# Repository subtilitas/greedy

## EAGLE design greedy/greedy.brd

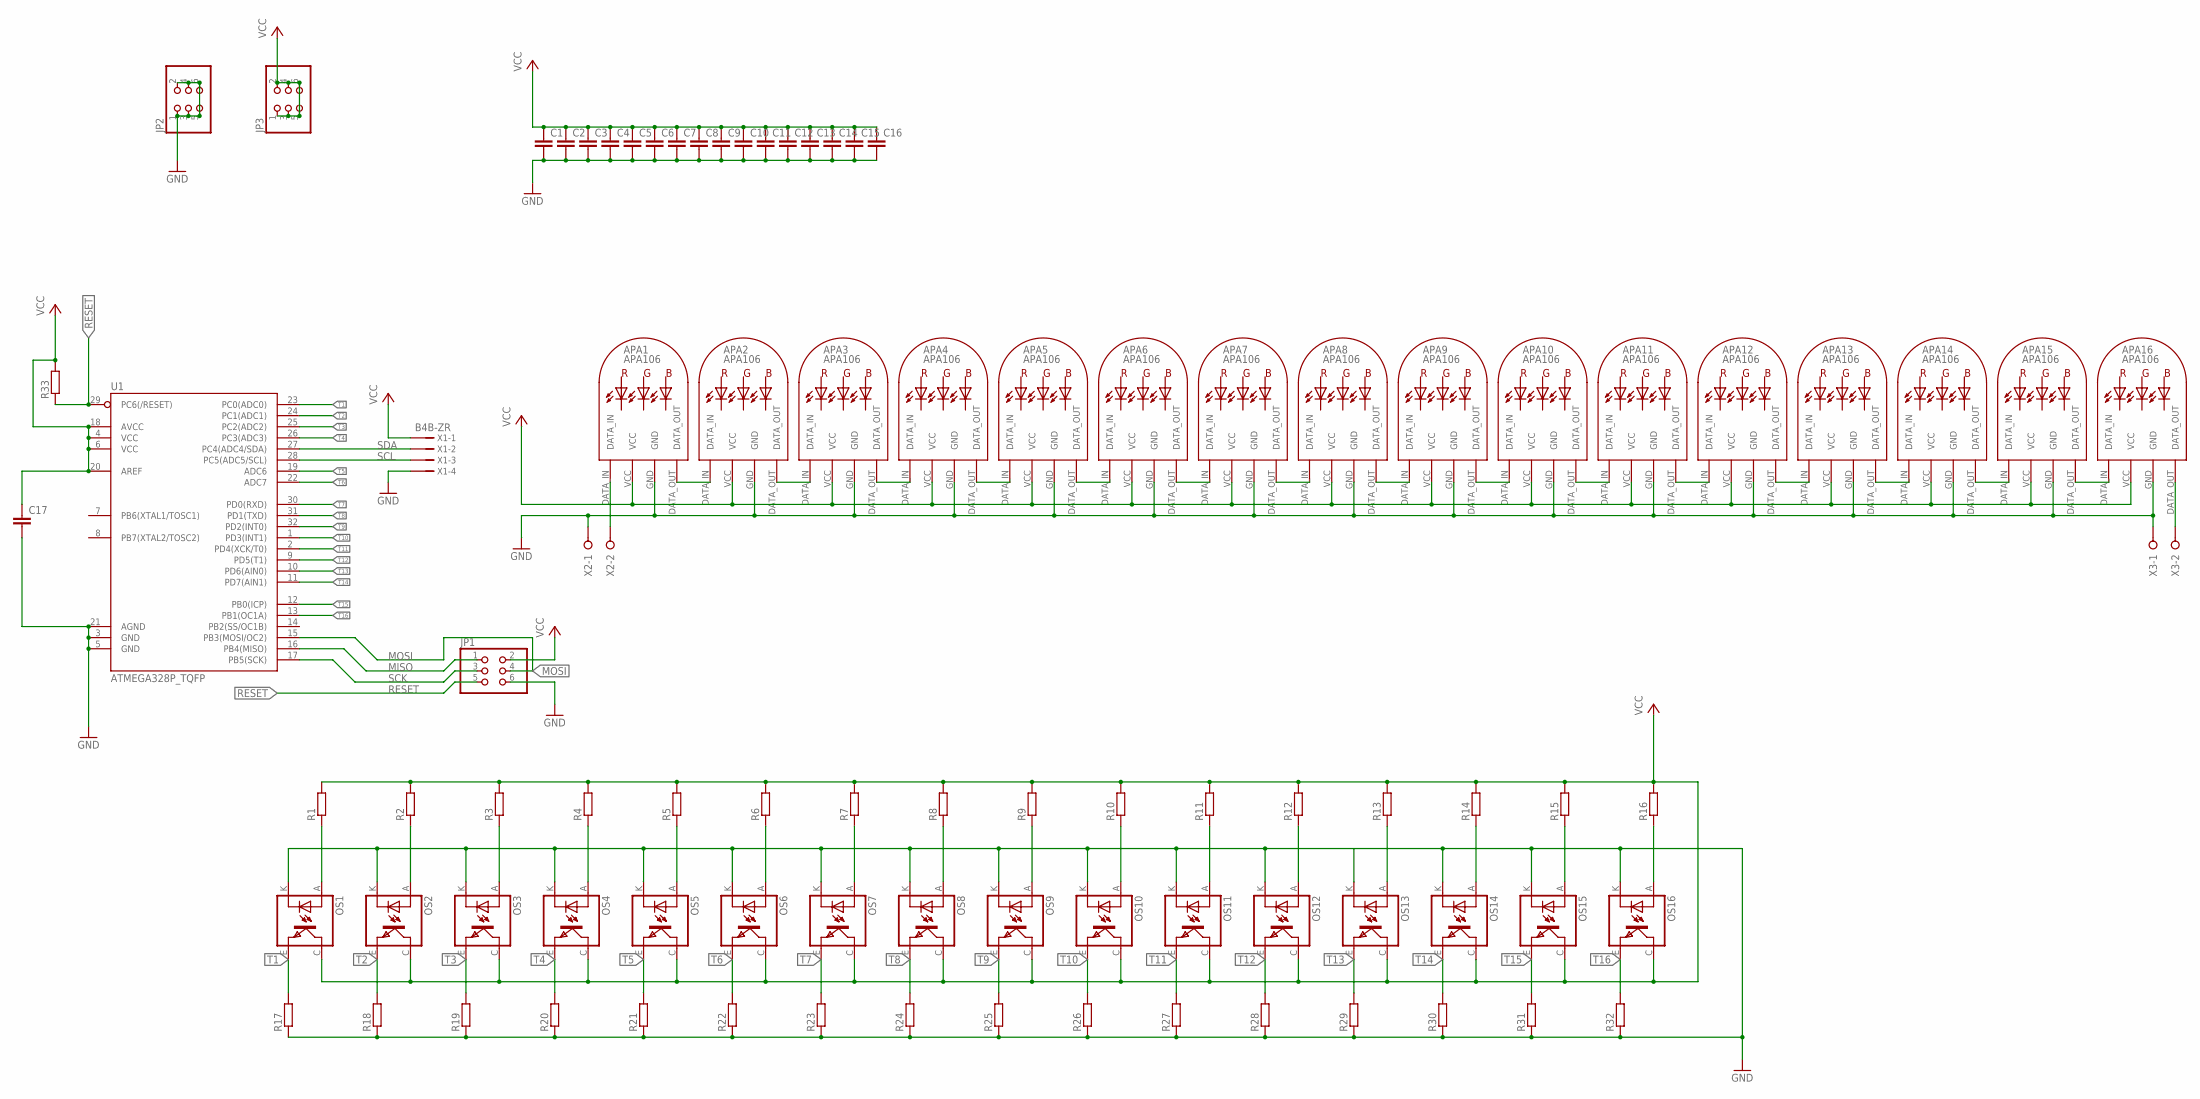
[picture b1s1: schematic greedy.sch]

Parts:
APA1, APA2, APA3, APA4, APA5, APA6, APA7, APA8, APA9, APA10, APA11, APA12, APA13, APA14, APA15, APA16: APA106; APA_106_8MM
C1, C2, C3, C4, C5, C6, C7, C8, C9, C10, C11, C12, C13, C14, C15, C16: C5/3; C5B3
C17: C-EU025-025X050; C025-025X050
JP1, JP2, JP3: PINHD-2X3; 2X03
OS1, OS2, OS3, OS4, OS5, OS6, OS7, OS8, OS9, OS10, OS11, OS12, OS13, OS14, OS15, OS16: TCRT5000
R1, R2, R3, R4, R5, R6, R7, R8, R9, R10, R11, R12, R13, R14, R15, R16, R17, R18, R19, R20, R21, R22, R23, R24, R25, R26, R27, R28, R29, R30, R31, R32, R33: R-EU_R0805; R0805
U1: ATMEGA328P_TQFP; TQFP32-08
X1: B4B-ZR
X2, X3: W237-02P; W237-132

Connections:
GND: APA1.GND, APA2.GND, APA3.GND, APA4.GND, APA5.GND, APA6.GND, APA7.GND, APA8.GND, APA9.GND, APA10.GND, APA11.GND, APA12.GND, APA13.GND, APA14.GND, APA15.GND, APA16.GND, C1.2, C2.2, C3.2, C4.2, C5.2, C6.2, C7.2, C8.2, C9.2, C10.2, C11.2, C12.2, C13.2, C14.2, C15.2, C16.2, C17.2, JP1.6, JP2.1, JP2.2, JP2.3, JP2.4, JP2.5, JP2.6, OS1.K (CATHODE), OS2.K (CATHODE), OS3.K (CATHODE), OS4.K (CATHODE), OS5.K (CATHODE), OS6.K (CATHODE), OS7.K (CATHODE), OS8.K (CATHODE), OS9.K (CATHODE), OS10.K (CATHODE), OS11.K (CATHODE), OS12.K (CATHODE), OS13.K (CATHODE), OS14.K (CATHODE), OS15.K (CATHODE), OS16.K (CATHODE), R17.1, R17.11 (1), R18.1, R18.11 (1), R19.1, R19.11 (1), R20.1, R20.11 (1), R21.1, R21.11 (1), R22.1, R22.11 (1), R23.1, R23.11 (1), R24.1, R24.11 (1), R25.1, R25.11 (1), R26.1, R26.11 (1), R27.1, R27.11 (1), R28.1, R28.11 (1), R29.1, R29.11 (1), R30.1, R30.11 (1), R31.1, R31.11 (1), R32.1, R32.11 (1), U1.3 (GND), U1.5 (GND), U1.21 (AGND), X1.4, X2.1, X3.1
MISO: JP1.1, U1.16 (PB4(MISO))
MOSI: JP1.4, U1.15 (PB3(MOSI/OC2))
unnamed: APA1.DATA_IN, X2.2
unnamed: OS1.A (ANODE), R1.1, R1.11 (1)
unnamed: OS2.A (ANODE), R2.1, R2.11 (1)
unnamed: OS3.A (ANODE), R3.1, R3.11 (1)
unnamed: OS4.A (ANODE), R4.1, R4.11 (1)
unnamed: OS5.A (ANODE), R5.1, R5.11 (1)
unnamed: OS6.A (ANODE), R6.1, R6.11 (1)
unnamed: OS7.A (ANODE), R7.1, R7.11 (1)
unnamed: OS8.A (ANODE), R8.1, R8.11 (1)
unnamed: OS9.A (ANODE), R9.1, R9.11 (1)
unnamed: OS10.A (ANODE), R10.1, R10.11 (1)
unnamed: OS11.A (ANODE), R11.1, R11.11 (1)
unnamed: OS12.A (ANODE), R12.1, R12.11 (1)
unnamed: OS13.A (ANODE), R13.1, R13.11 (1)
unnamed: OS14.A (ANODE), R14.1, R14.11 (1)
unnamed: OS15.A (ANODE), R15.1, R15.11 (1)
unnamed: OS16.A (ANODE), R16.1, R16.11 (1)
unnamed: APA16.DATA_OUT, X3.2
unnamed: APA1.DATA_OUT, APA2.DATA_IN
unnamed: APA2.DATA_OUT, APA3.DATA_IN
unnamed: APA3.DATA_OUT, APA4.DATA_IN
unnamed: APA4.DATA_OUT, APA5.DATA_IN
unnamed: APA5.DATA_OUT, APA6.DATA_IN
unnamed: APA6.DATA_OUT, APA7.DATA_IN
unnamed: APA7.DATA_OUT, APA8.DATA_IN
unnamed: APA8.DATA_OUT, APA9.DATA_IN
unnamed: APA9.DATA_OUT, APA10.DATA_IN
unnamed: APA10.DATA_OUT, APA11.DATA_IN
unnamed: APA11.DATA_OUT, APA12.DATA_IN
unnamed: APA12.DATA_OUT, APA13.DATA_IN
unnamed: APA13.DATA_OUT, APA14.DATA_IN
unnamed: APA14.DATA_OUT, APA15.DATA_IN
unnamed: APA15.DATA_OUT, APA16.DATA_IN
RESET: JP1.5, R33.1, R33.11 (1), U1.29 (PC6(/RESET))
SCK: JP1.3, U1.17 (PB5(SCK))
SCL: U1.28 (PC5(ADC5/SCL)), X1.3
SDA: U1.27 (PC4(ADC4/SDA)), X1.2
T1: OS1.E (EMITTER), R17.2, R17.21 (2), U1.23 (PC0(ADC0))
T2: OS2.E (EMITTER), R18.2, R18.21 (2), U1.24 (PC1(ADC1))
T3: OS3.E (EMITTER), R19.2, R19.21 (2), U1.25 (PC2(ADC2))
T4: OS4.E (EMITTER), R20.2, R20.21 (2), U1.26 (PC3(ADC3))
T5: OS5.E (EMITTER), R21.2, R21.21 (2), U1.19 (ADC6)
T6: OS6.E (EMITTER), R22.2, R22.21 (2), U1.22 (ADC7)
T7: OS7.E (EMITTER), R23.2, R23.21 (2), U1.30 (PD0(RXD))
T8: OS8.E (EMITTER), R24.2, R24.21 (2), U1.31 (PD1(TXD))
T9: OS9.E (EMITTER), R25.2, R25.21 (2), U1.32 (PD2(INT0))
T10: OS10.E (EMITTER), R26.2, R26.21 (2), U1.1 (PD3(INT1))
T11: OS11.E (EMITTER), R27.2, R27.21 (2), U1.2 (PD4(XCK/T0))
T12: OS12.E (EMITTER), R28.2, R28.21 (2), U1.9 (PD5(T1))
T13: OS13.E (EMITTER), R29.2, R29.21 (2), U1.10 (PD6(AIN0))
T14: OS14.E (EMITTER), R30.2, R30.21 (2), U1.11 (PD7(AIN1))
T15: OS15.E (EMITTER), R31.2, R31.21 (2), U1.12 (PB0(ICP))
T16: OS16.E (EMITTER), R32.2, R32.21 (2), U1.13 (PB1(OC1A))
VCC: APA1.VCC, APA2.VCC, APA3.VCC, APA4.VCC, APA5.VCC, APA6.VCC, APA7.VCC, APA8.VCC, APA9.VCC, APA10.VCC, APA11.VCC, APA12.VCC, APA13.VCC, APA14.VCC, APA15.VCC, APA16.VCC, C1.1, C2.1, C3.1, C4.1, C5.1, C6.1, C7.1, C8.1, C9.1, C10.1, C11.1, C12.1, C13.1, C14.1, C15.1, C16.1, C17.1, JP1.2, JP3.1, JP3.2, JP3.3, JP3.4, JP3.5, JP3.6, OS1.C (COLLECTOR), OS2.C (COLLECTOR), OS3.C (COLLECTOR), OS4.C (COLLECTOR), OS5.C (COLLECTOR), OS6.C (COLLECTOR), OS7.C (COLLECTOR), OS8.C (COLLECTOR), OS9.C (COLLECTOR), OS10.C (COLLECTOR), OS11.C (COLLECTOR), OS12.C (COLLECTOR), OS13.C (COLLECTOR), OS14.C (COLLECTOR), OS15.C (COLLECTOR), OS16.C (COLLECTOR), R1.2, R1.21 (2), R2.2, R2.21 (2), R3.2, R3.21 (2), R4.2, R4.21 (2), R5.2, R5.21 (2), R6.2, R6.21 (2), R7.2, R7.21 (2), R8.2, R8.21 (2), R9.2, R9.21 (2), R10.2, R10.21 (2), R11.2, R11.21 (2), R12.2, R12.21 (2), R13.2, R13.21 (2), R14.2, R14.21 (2), R15.2, R15.21 (2), R16.2, R16.21 (2), R33.2, R33.21 (2), U1.4 (VCC), U1.6 (VCC), U1.18 (AVCC), U1.20 (AREF), X1.1

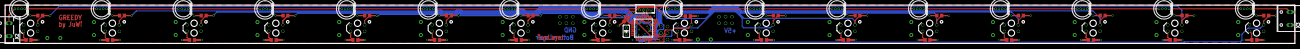
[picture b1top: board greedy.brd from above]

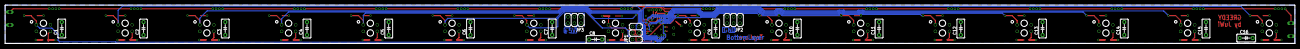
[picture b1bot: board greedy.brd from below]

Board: 4 copper layers, 505.0 x 15.0 mm, 89 parts (19 on the bottom side), 57 nets.

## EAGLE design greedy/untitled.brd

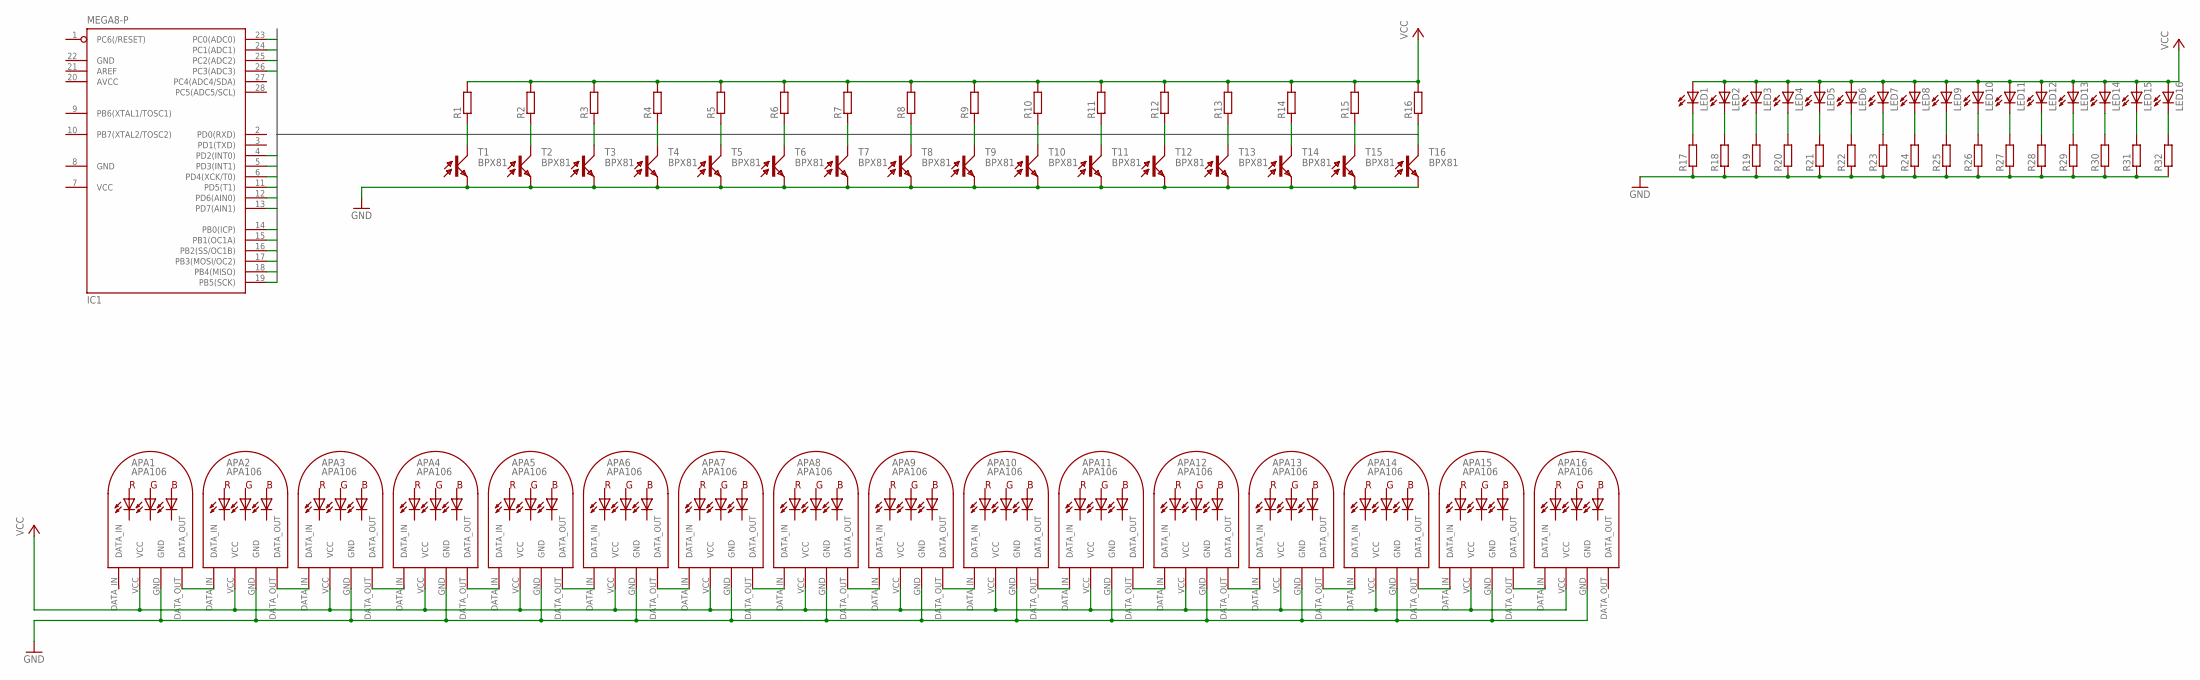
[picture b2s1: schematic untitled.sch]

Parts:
APA1, APA2, APA3, APA4, APA5, APA6, APA7, APA8, APA9, APA10, APA11, APA12, APA13, APA14, APA15, APA16: APA106; APA_106_8MM
IC1: MEGA8-P; DIL28-3
LED1, LED2, LED3, LED4, LED5, LED6, LED7, LED8, LED9, LED10, LED11, LED12, LED13, LED14, LED15, LED16: LEDLZR181; LZR181
R1, R2, R3, R4, R5, R6, R7, R8, R9, R10, R11, R12, R13, R14, R15, R16, R17, R18, R19, R20, R21, R22, R23, R24, R25, R26, R27, R28, R29, R30, R31, R32: R-EU_R0603; R0603
T1, T2, T3, T4, T5, T6, T7, T8, T9, T10, T11, T12, T13, T14, T15, T16: BPX81

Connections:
AVCC: IC1.20 (AVCC)
GND: APA1.GND, APA2.GND, APA3.GND, APA4.GND, APA5.GND, APA6.GND, APA7.GND, APA8.GND, APA9.GND, APA10.GND, APA11.GND, APA12.GND, APA13.GND, APA14.GND, APA15.GND, APA16.GND, IC1.8 (GND), IC1.22 (GND), R17.1, R18.1, R19.1, R20.1, R21.1, R22.1, R23.1, R24.1, R25.1, R26.1, R27.1, R28.1, R29.1, R30.1, R31.1, R32.1, T1.E, T2.E, T3.E, T4.E, T5.E, T6.E, T7.E, T8.E, T9.E, T10.E, T11.E, T12.E, T13.E, T14.E, T15.E, T16.E
unnamed: APA1.DATA_OUT, APA2.DATA_IN
unnamed: APA2.DATA_OUT, APA3.DATA_IN
unnamed: APA3.DATA_OUT, APA4.DATA_IN
unnamed: APA4.DATA_OUT, APA5.DATA_IN
unnamed: APA5.DATA_OUT, APA6.DATA_IN
unnamed: APA6.DATA_OUT, APA7.DATA_IN
unnamed: APA7.DATA_OUT, APA8.DATA_IN
unnamed: APA8.DATA_OUT, APA9.DATA_IN
unnamed: APA9.DATA_OUT, APA10.DATA_IN
unnamed: APA10.DATA_OUT, APA11.DATA_IN
unnamed: APA11.DATA_OUT, APA12.DATA_IN
unnamed: APA12.DATA_OUT, APA13.DATA_IN
unnamed: APA13.DATA_OUT, APA14.DATA_IN
unnamed: APA14.DATA_OUT, APA15.DATA_IN
unnamed: APA15.DATA_OUT, APA16.DATA_IN
unnamed: LED1.K (C), R17.2
unnamed: LED2.K (C), R18.2
unnamed: LED3.K (C), R19.2
unnamed: LED4.K (C), R20.2
unnamed: LED5.K (C), R21.2
unnamed: LED6.K (C), R22.2
unnamed: LED7.K (C), R23.2
unnamed: LED8.K (C), R24.2
unnamed: LED9.K (C), R25.2
unnamed: LED10.K (C), R26.2
unnamed: LED11.K (C), R27.2
unnamed: LED12.K (C), R28.2
unnamed: LED13.K (C), R29.2
unnamed: LED14.K (C), R30.2
unnamed: LED15.K (C), R31.2
unnamed: LED16.K (C), R32.2
PT1: IC1.23 (PC0(ADC0)), R1.1, T1.C
PT2: IC1.24 (PC1(ADC1)), R2.1, T2.C
PT3: IC1.25 (PC2(ADC2)), R3.1, T3.C
PT4: IC1.26 (PC3(ADC3)), R4.1, T4.C
PT5: IC1.18 (PB4(MISO)), R5.1, T5.C
PT6: IC1.19 (PB5(SCK)), R6.1, T6.C
PT7: IC1.4 (PD2(INT0)), R7.1, T7.C
PT8: IC1.5 (PD3(INT1)), R8.1, T8.C
PT9: IC1.6 (PD4(XCK/T0)), R9.1, T9.C
PT10: IC1.11 (PD5(T1)), R10.1, T10.C
PT11: IC1.12 (PD6(AIN0)), R11.1, T11.C
PT12: IC1.13 (PD7(AIN1)), R12.1, T12.C
PT13: IC1.14 (PB0(ICP)), R13.1, T13.C
PT14: IC1.15 (PB1(OC1A)), R14.1, T14.C
PT15: IC1.16 (PB2(SS/OC1B)), R15.1, T15.C
PT16: IC1.17 (PB3(MOSI/OC2)), R16.1, T16.C
VCC: APA1.VCC, APA2.VCC, APA3.VCC, APA4.VCC, APA5.VCC, APA6.VCC, APA7.VCC, APA8.VCC, APA9.VCC, APA10.VCC, APA11.VCC, APA12.VCC, APA13.VCC, APA14.VCC, APA15.VCC, APA16.VCC, IC1.7 (VCC), LED1.A, LED2.A, LED3.A, LED4.A, LED5.A, LED6.A, LED7.A, LED8.A, LED9.A, LED10.A, LED11.A, LED12.A, LED13.A, LED14.A, LED15.A, LED16.A, R1.2, R2.2, R3.2, R4.2, R5.2, R6.2, R7.2, R8.2, R9.2, R10.2, R11.2, R12.2, R13.2, R14.2, R15.2, R16.2

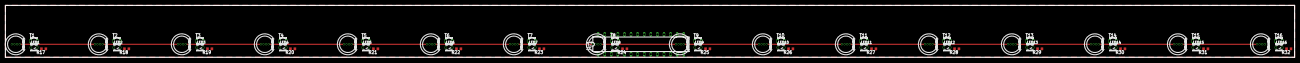
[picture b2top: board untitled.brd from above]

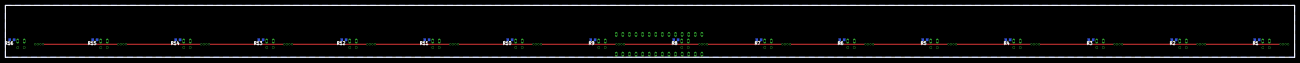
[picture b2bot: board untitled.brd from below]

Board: 2 copper layers, 497.0 x 20.0 mm, 81 parts (16 on the bottom side), 49 nets.

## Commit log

2017-12-30 initial wondows tests
2018-01-01 some working version
2018-01-01 first order...

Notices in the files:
parts and their libraries:
SparkFun-IC-Microcontroller: Licensing: Creative Commons ShareAlike 4.0 International - https://creativecommons.org/licenses/by-sa/4.0
